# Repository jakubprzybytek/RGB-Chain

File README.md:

#### ToDo
* Fix 3V3 / 5V converter so it works faster

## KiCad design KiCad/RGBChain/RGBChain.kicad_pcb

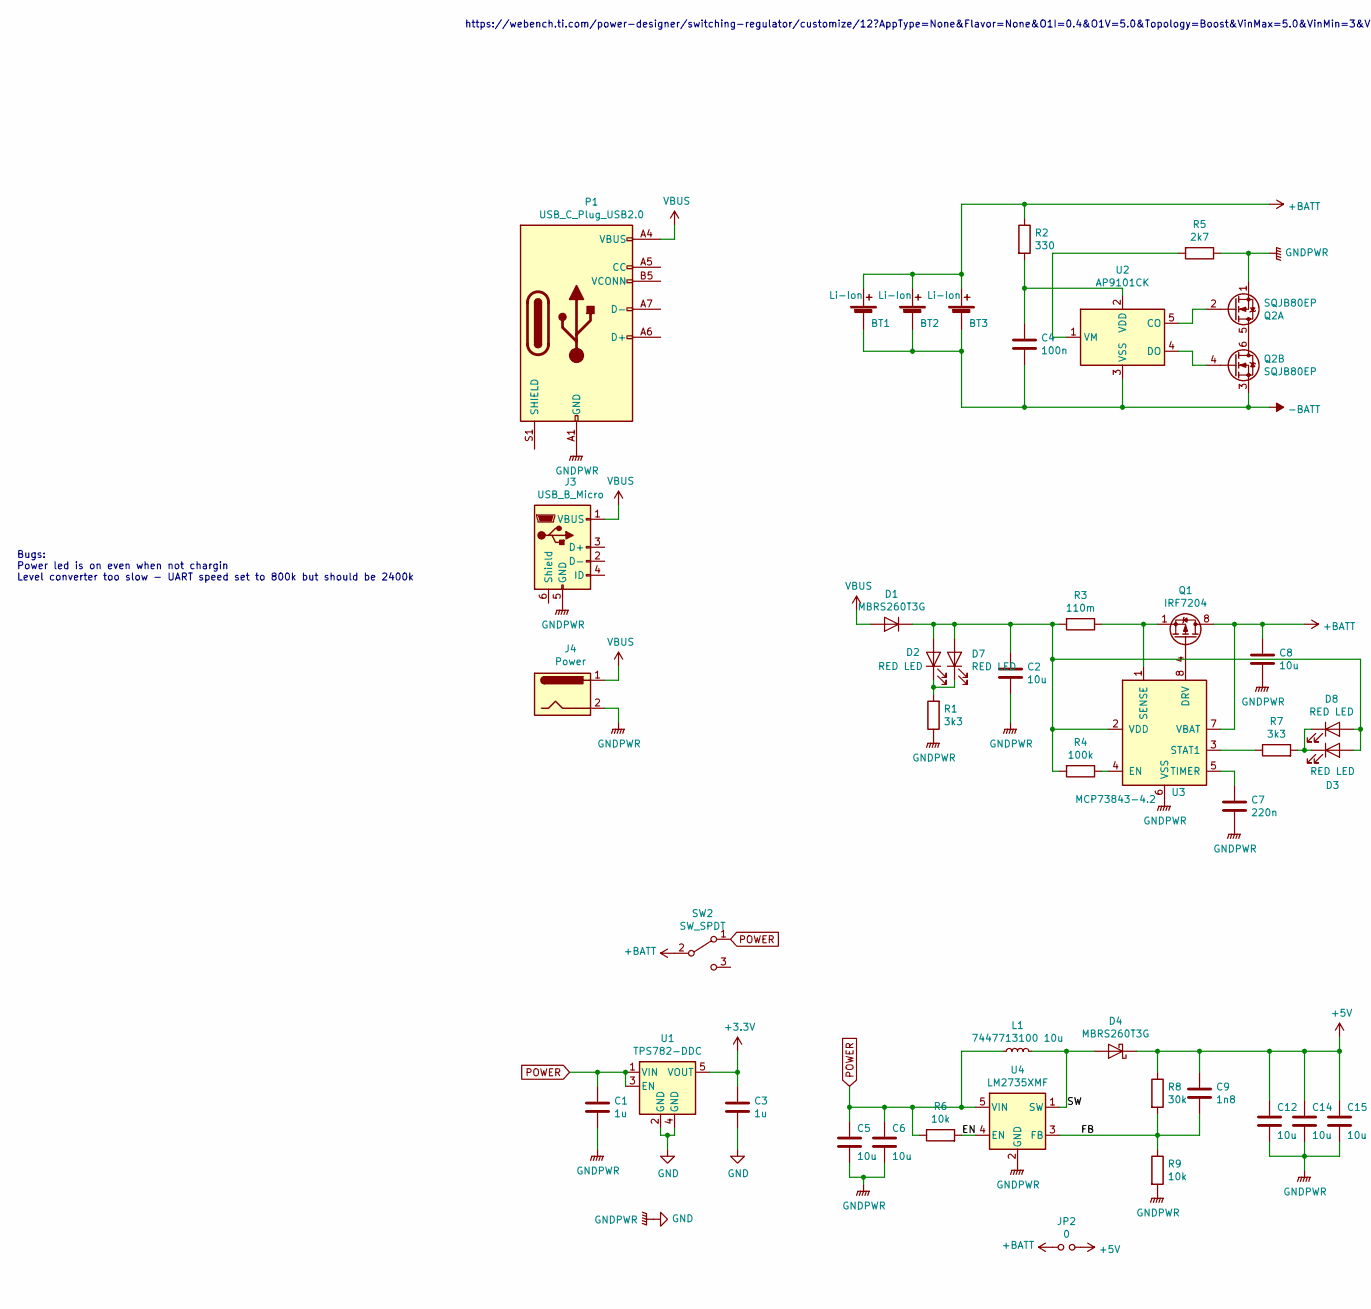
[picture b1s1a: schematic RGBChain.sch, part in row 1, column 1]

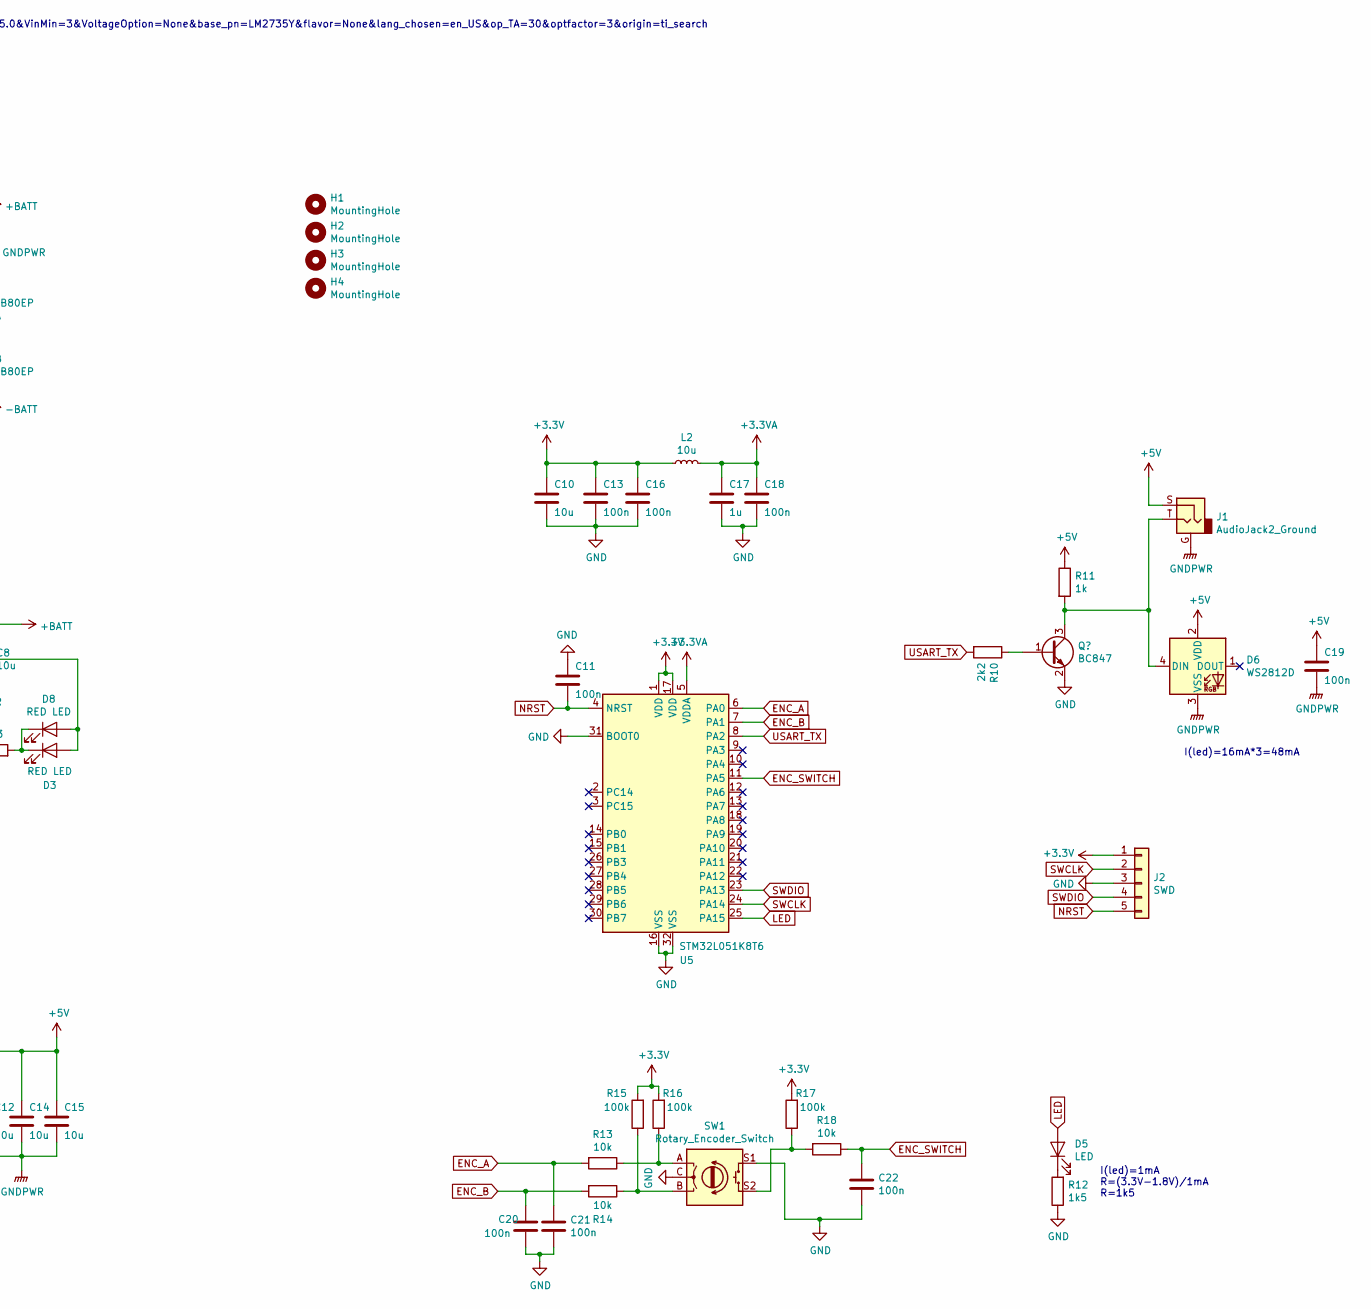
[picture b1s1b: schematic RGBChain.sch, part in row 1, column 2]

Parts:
BT1, BT2, BT3: Li-Ion; BatteryHolder_Keystone_1042_1x18650
C1, C3, C17: 1u; C_0805_2012Metric
C2, C5, C6, C8, C10, C12, C14, C15: 10u; C_0805_2012Metric
C4, C11, C13, C16, C18, C19, C20, C21, C22: 100n; C_0603_1608Metric
C7: 220n; C_0805_2012Metric
C9: 1n8; C_0805_2012Metric
D1, D4: MBRS260T3G; D_SMB
D2, D3: RED LED; LED_0805_2012Metric
D5: LED; LED_0805_2012Metric
D6: WS2812D; LED_D5.0mm-4_RGB
D7, D8: RED LED; LED_D3.0mm
H1, H2, H3, H4: MountingHole; MountingHole_3.2mm_M3
J1: AudioJack2_Ground; Jack_3.5mm_Lumberg_1503_03
J2: SWD; PinHeader_1x05_P2.54mm_Vertical
J3: USB_B_Micro; USB_Micro-B_Molex_47346-0001
J4: Power; PowerSocketSMD
JP2: 0; SolderJumper-2_P1.3mm_Open_Pad1.0x1.5mm
L1: 7447713100 10u; L_Wuerth_WE-PDF_Handsoldering
L2: 10u; L_0805_2012Metric
P1: USB_C_Plug_USB2.0; USB_C_Receptacle_Adam_Tech
Q1: IRF7204; SOIC-8_3.9x4.9mm_P1.27mm
Q2: SQJB80EP; PowerPAK_SO-8_Dual
R1, R7: 3k3; R_0805_2012Metric
R2: 330; R_0805_2012Metric
R3: 110m; R_2512_6332Metric
R4, R15, R16, R17: 100k; R_0603_1608Metric
R5: 2k7; R_0805_2012Metric
R6, R13, R14, R18: 10k; R_0603_1608Metric
R8: 30k; R_0805_2012Metric
R9: 10k; R_0805_2012Metric
R10: 2k2; R_0603_1608Metric
R11: 1k; R_0805_2012Metric
R12: 1k5; R_0805_2012Metric
SW1: Rotary_Encoder_Switch; RotaryEncoder_Alps_EC11E-Switch_Vertical_H20mm_CircularMoun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
SW2: SW_SPDT; NINIGI_5F_M6
U1: TPS782-DDC; SOT-23-5
U2: AP9101CK; SOT-23-5
U3: MCP73843-4.2; MSOP-8_3x3mm_P0.65mm
U4: LM2735XMF; SOT-23-5
U5: STM32L051K8T6; LQFP-32_7x7mm_P0.8mm

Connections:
+3.3VA: C17.1, C18.1, L2.2, U5.5 (VDDA)
+3V3: C3.1, C10.1, C13.1, C16.1, J2.1, L2.1, R15.2, R16.2, R17.2, U1.5 (VOUT), U5.1 (VDD), U5.17 (VDD)
+5V: C9.1, C12.1, C14.1, C15.1, C19.1, D4.1 (K), D6.2 (VDD), J1.S, JP2.2, R8.1, R11.1
+BATT: BT1.1 (+), BT2.1 (+), BT3.1 (+), C8.1, JP2.1, Q1.5 (D), Q1.6 (D), Q1.7 (D), Q1.8 (D), R2.1, SW2.2 (B), U3.7 (VBAT)
-BATT: BT1.2 (-), BT2.2 (-), BT3.2 (-), C4.2, Q2.3 (S2), U2.3 (VSS)
/EN: R6.2, U4.4 (EN)
/FB: C9.2, R8.2, R9.1, U4.3 (FB)
/SW: D4.2 (A), L1.2, U4.1 (SW)
ENC_A: C21.1, R13.2, U5.6 (PA0)
ENC_B: C20.1, R14.2, U5.7 (PA1)
ENC_SWITCH: C22.1, R18.1, U5.11 (PA5)
LED: D5.2 (A), U5.25 (PA15)
NRST: C11.2, J2.5, U5.4 (NRST)
unnamed: C2.1, D1.1 (K), D2.2 (A), D3.2 (A), D7.2 (A), D8.2 (A), R3.2, R4.2, U3.2 (VDD)
unnamed: C4.1, R2.2, U2.2 (VDD)
unnamed: C7.1, U3.5 (TIMER)
unnamed: D2.1 (K), D7.1 (K), R1.2
unnamed: D3.1 (K), D8.1 (K), R7.2
unnamed: D5.1 (K), R12.2
unnamed 20: D6.4 (DIN), J1.T, R11.2; also elsewhere on the board
unnamed: Q1.1 (S), Q1.2 (S), Q1.3 (S), R3.1, U3.1 (SENSE)
unnamed: Q1.4 (G), U3.8 (DRV)
unnamed: Q2.2 (G2), U2.5 (CO)
unnamed: Q2.4 (G2), U2.4 (DO)
unnamed: Q2.5 (D2), Q2.6 (D2)
unnamed: R4.1, U3.4 (EN)
unnamed: R5.2, U2.1 (VM)
unnamed: R7.1, U3.3 (STAT1)
unnamed: R13.1, R16.1, SW1.A
unnamed: R14.1, R15.1, SW1.B
unnamed: R17.1, R18.2, SW1.S2
POWER: C1.1, C5.1, C6.1, L1.1, R6.1, SW2.1 (A), U1.1 (VIN), U1.3 (EN), U4.5 (VIN)
SWCLK: J2.2, U5.24 (PA14)
SWDIO: J2.4, U5.23 (PA13)
VBUS: D1.2 (A), J3.1 (VBUS), J4.1, P1.A4 (VBUS), P1.A9 (VBUS), P1.B4 (VBUS), P1.B9 (VBUS)

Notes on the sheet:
I(led)=1mA R=(3.3V-1.8V)/1mA R=1k5
https://webench.ti.com/power-designer/switching-regulator/customize/12?AppType=None&Flavor=None&O1I=0.4&O1V=5.0&Topology=Boost&VinMax=5.0&VinMin=3&VoltageOption=None&base_pn=LM2735Y&flavor=None&lang_chosen=en_US&op_TA=30&optfactor=3&origin=ti_search
I(led)=16mA*3=48mA
Bugs: Power led is on even when not chargin Level converter too slow - UART speed set to 800k but should be 2400k

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
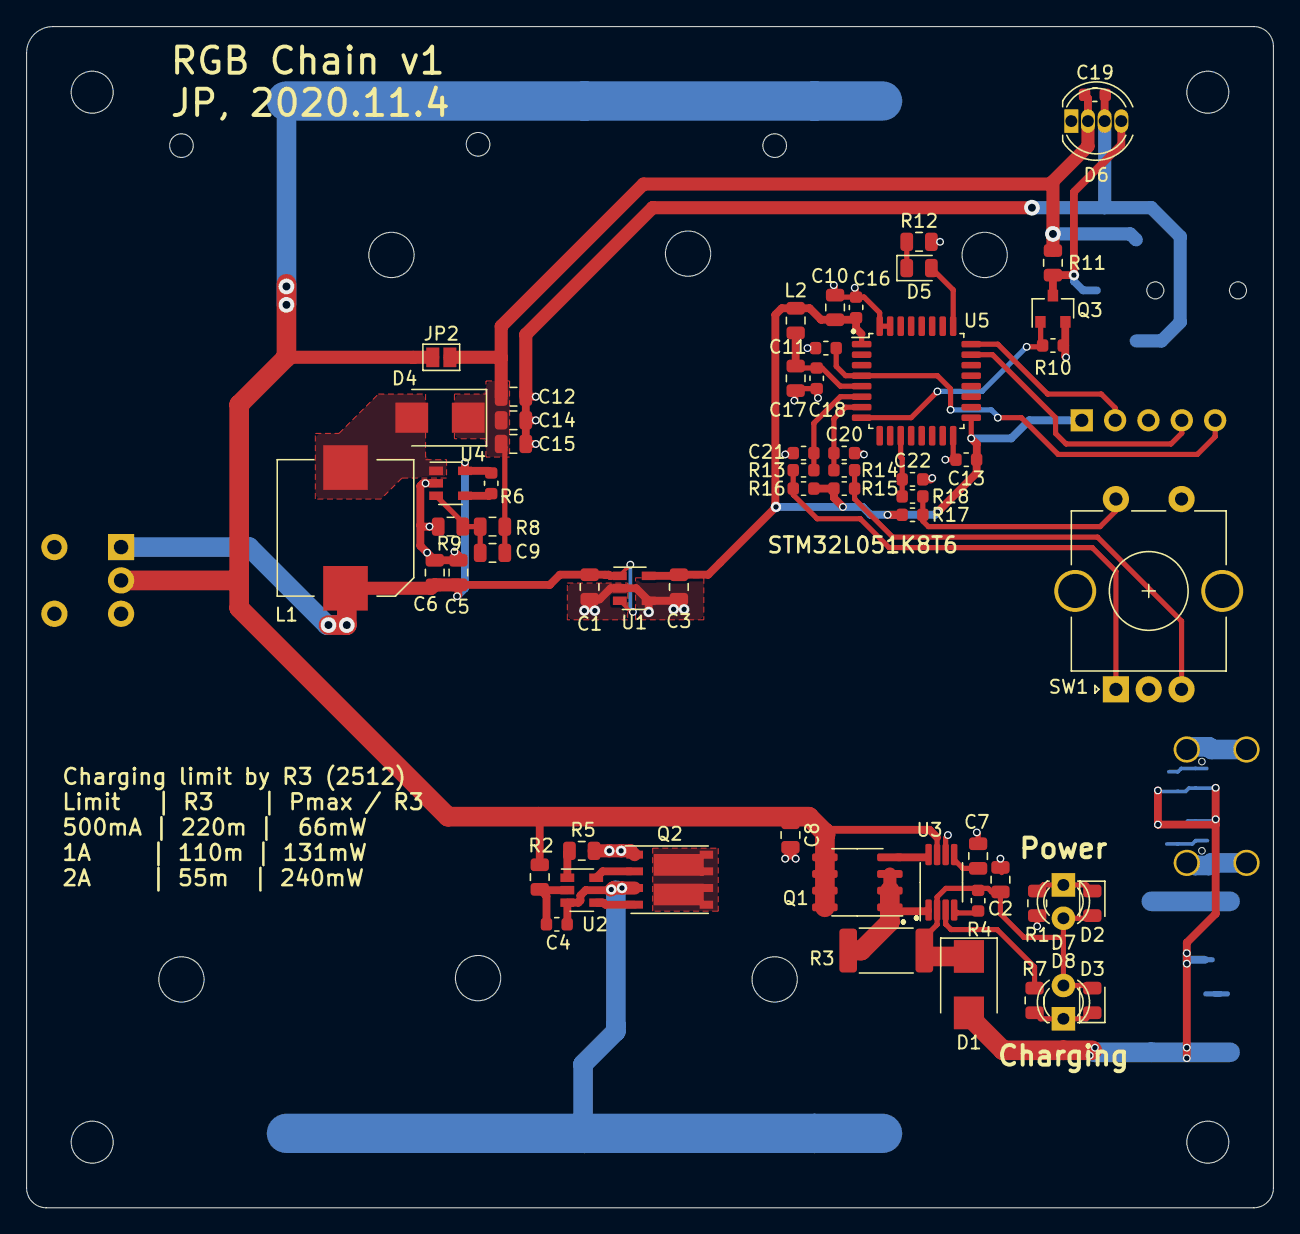
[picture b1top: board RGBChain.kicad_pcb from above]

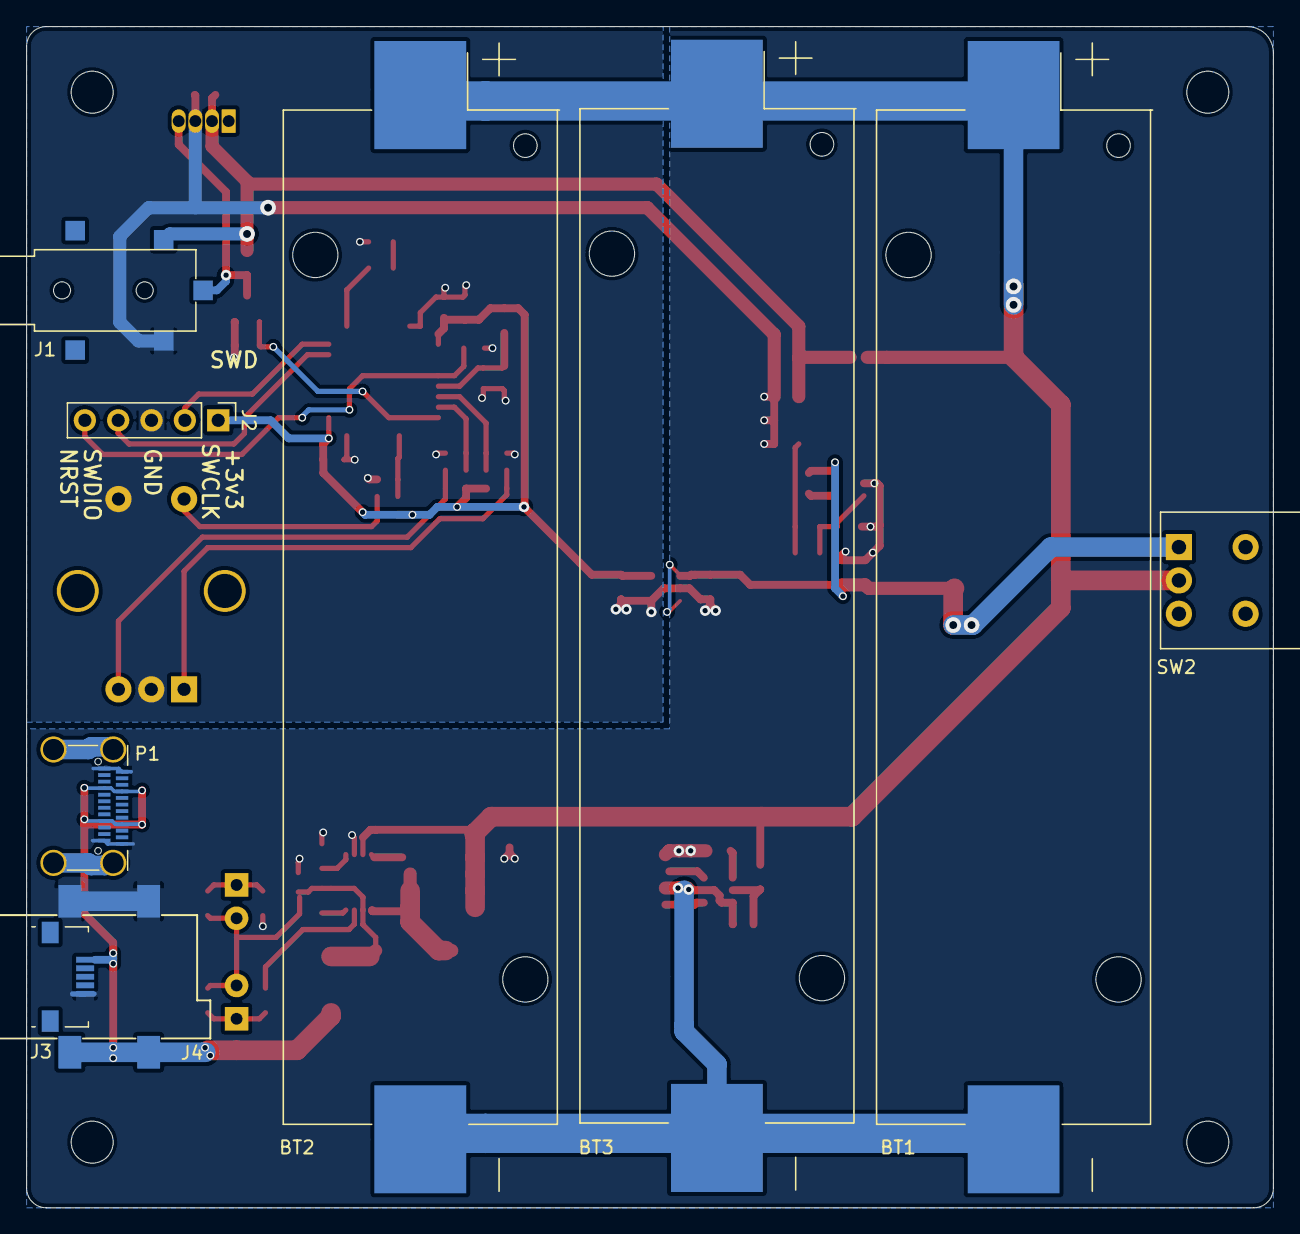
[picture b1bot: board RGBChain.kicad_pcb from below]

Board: 2 copper layers, 95.0 x 90.0 mm, 73 parts (9 on the bottom side), 37 nets.

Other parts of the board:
Q3: IRLML2502; SOT-23

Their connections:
unnamed 20: Q3.3; also elsewhere on the board

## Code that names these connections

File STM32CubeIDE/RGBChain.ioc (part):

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Mcu.Name=STM32L010K8Tx
Mcu.Package=LQFP32
Mcu.UserName=STM32L010K8Tx
PA0.GPIOParameters=GPIO_Speed,GPIO_PuPd,GPIO_Label
PA0.GPIO_Label=EncoderA
PA0.GPIO_PuPd=GPIO_PULLUP
PA0.GPIO_Speed=GPIO_SPEED_FREQ_HIGH
PA0.Signal=S_TIM2_CH1
PA1.GPIOParameters=GPIO_Speed,GPIO_PuPd,GPIO_Label
PA1.GPIO_Label=EncoderB
PA1.GPIO_PuPd=GPIO_PULLUP
PA1.GPIO_Speed=GPIO_SPEED_FREQ_HIGH
PA1.Signal=S_TIM2_CH2
PA13.Mode=Serial_Wire
PA13.Signal=SYS_SWDIO
PA14.Mode=Serial_Wire
PA14.Signal=SYS_SWCLK
PA15.GPIOParameters=GPIO_Label
PA15.GPIO_Label=Led
PA15.Signal=GPIO_Output
PA2.GPIOParameters=GPIO_Label
PA2.GPIO_Label=WS2812
PA2.Mode=Asynchronous
PA2.Signal=USART2_TX
PA3.Mode=Asynchronous
PA3.Signal=USART2_RX
PA5.GPIOParameters=GPIO_Label,GPIO_ModeDefaultEXTI
PA5.GPIO_Label=EncoderSwitch
PA5.GPIO_ModeDefaultEXTI=GPIO_MODE_IT_FALLING
PA5.Signal=GPXTI5
RCC.SYSCLKFreq_VALUE=32000000
RCC.SYSCLKSource=RCC_SYSCLKSOURCE_PLLCLK
board=custom

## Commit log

2020-10-24 Init commit
2020-10-25 PCB done
2020-10-30 PCB more work
2020-11-04 Last pcb changes
2020-12-08 Single colour effect implemented
2020-12-08 Second effect added: single static colout
2020-12-10 More work on effects
2020-12-11 Some refactoring with colours and encoder
2020-12-15 More effects. Refactoring
2020-12-17 Last tweaks
2021-01-01 Led tweaks
